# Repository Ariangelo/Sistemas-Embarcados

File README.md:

# Sistemas-Embarcados

Sistemas embarcados são parte integrante de muitos dispositivos de uso cotidiano. por exemplo:
* Sistema eletrônico computacional com propósito específico em controle de dispositivos
* Características importantes
    • Baixo consumo de energia
    • Tamanho reduzido
    • Baixo custopyth

* [Utizando o ESP8266](Documentos/ESP8266.pdf "Dados técnicos básicos para uso do ESP8266")

------

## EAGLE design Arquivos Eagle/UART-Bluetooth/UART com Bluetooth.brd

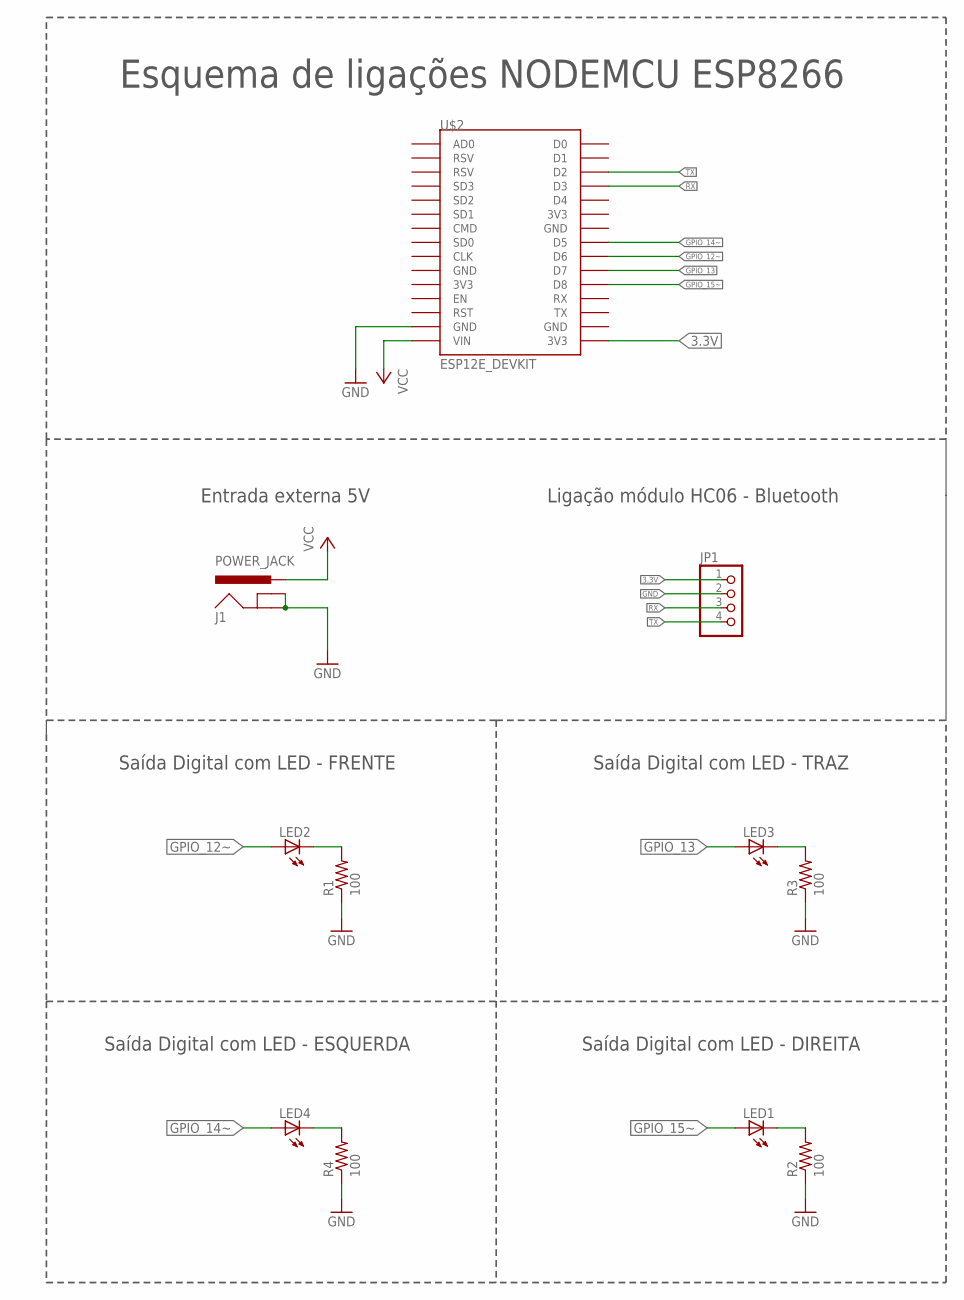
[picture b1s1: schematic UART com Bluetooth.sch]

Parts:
J1: POWER_JACK; POWER_JACK_PTH
JP1: PINHD-1X4; 1X04
LED1, LED2, LED3, LED4: LED5MM
R1, R2, R3, R4: 100; 0204/7
U$2: ESP12E_DEVKIT

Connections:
3.3V: JP1.1, U$2.3V3@2 (3V3)
GND: J1.GND, J1.GNDBREAK, JP1.2, R1.1, R2.1, R3.1, R4.1, U$2.GND@1 (GND)
GPIO_12~: LED2.A, U$2.D6
GPIO_13: LED3.A, U$2.D7
GPIO_14~: LED4.A, U$2.D5
GPIO_15~: LED1.A, U$2.D8
unnamed: LED2.K (C), R1.2
unnamed: LED3.K (C), R3.2
unnamed: LED4.K (C), R4.2
unnamed: LED1.K (C), R2.2
RX: JP1.3, U$2.D3
TX: JP1.4, U$2.D2
VCC: J1.PWR, U$2.VIN

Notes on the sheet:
Saída Digital com LED - DIREITA
Ligação módulo HC06 - Bluetooth
Entrada externa 5V
Esquema de ligações NODEMCU ESP8266
Saída Digital com LED - FRENTE
Saída Digital com LED - TRAZ
Saída Digital com LED - ESQUERDA

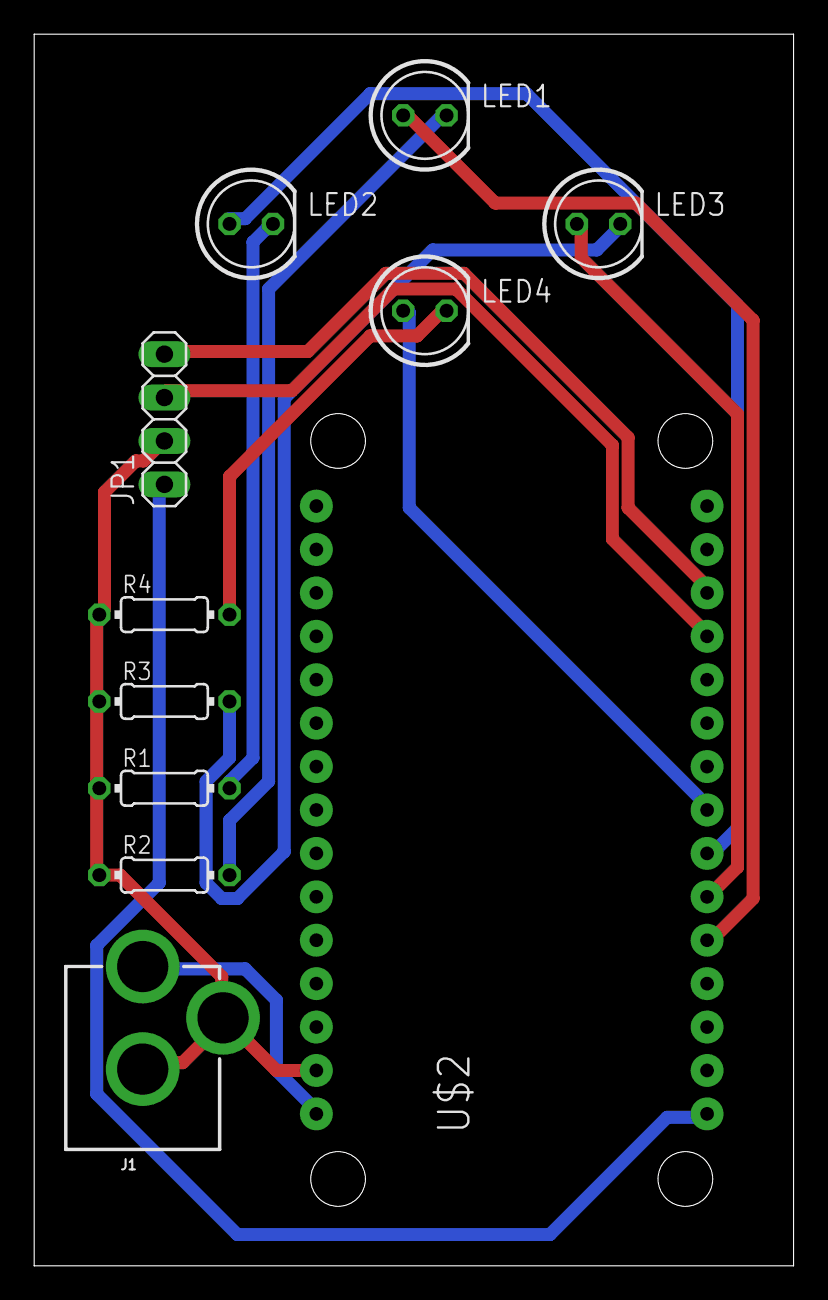
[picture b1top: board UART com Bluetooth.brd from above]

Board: 2 copper layers, 44.4 x 72.1 mm, 11 parts (0 on the bottom side), 13 nets.

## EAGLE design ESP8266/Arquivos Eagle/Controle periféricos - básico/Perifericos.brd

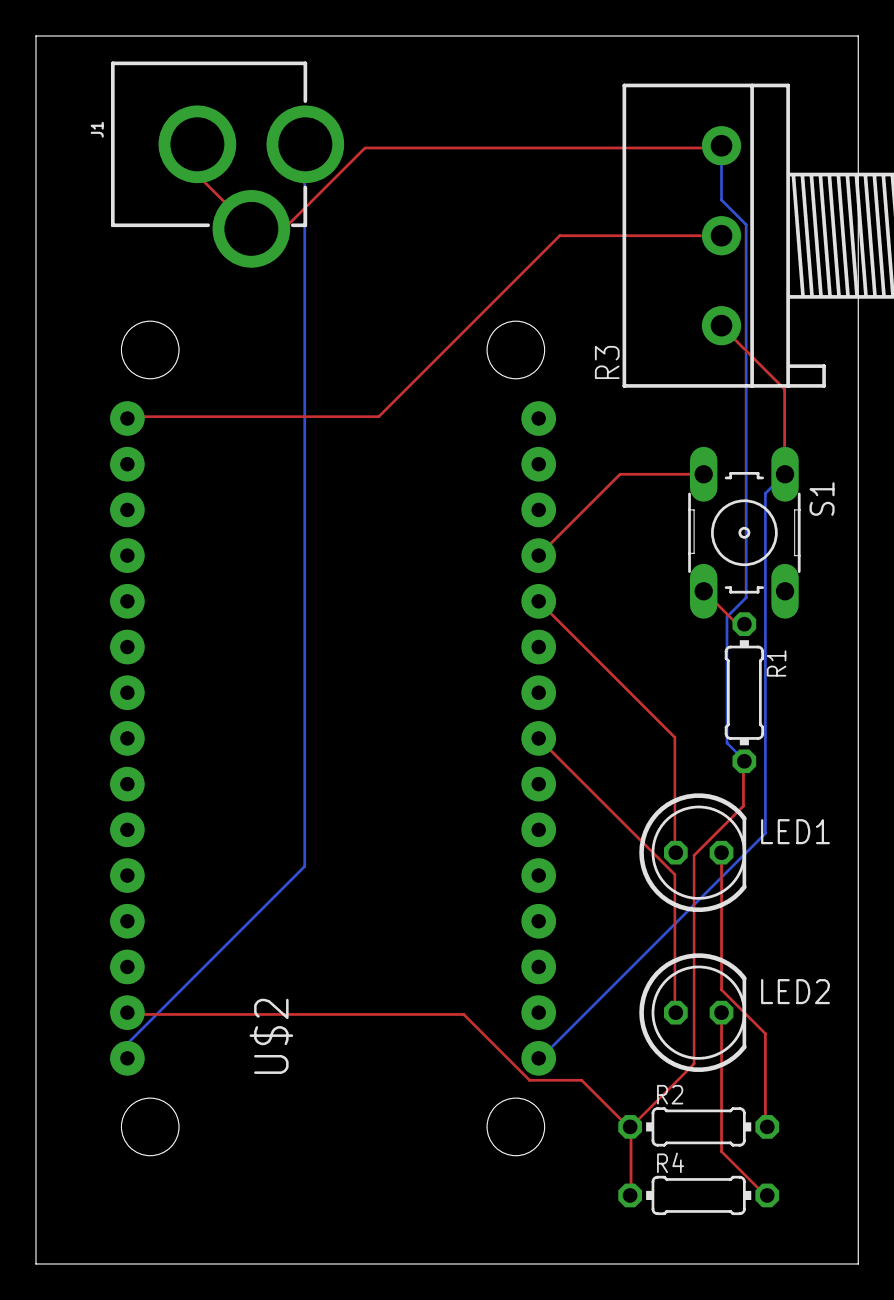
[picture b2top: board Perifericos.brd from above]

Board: 2 copper layers, 45.7 x 68.2 mm, 9 parts (0 on the bottom side), 10 nets.

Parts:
J1: POWER_JACK; POWER_JACK_PTH
LED1, LED2: LED5MM
R1: 100K; 0204/7
R2, R4: 100; 0204/7
R3: 3RP/1610N
S1: B3F-10XX
U$2: ESP12E_DEVKIT

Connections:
3.3V: R3.1, S1.1, U$2.3V3@2
ANALOG: R3.2, U$2.AD0
GND: J1.GND, J1.GNDBREAK, R1.2, R2.1, R3.3, R4.1, U$2.GND@1
GPIO_0: S1.3, U$2.D3
GPIO_2: LED1.A, U$2.D4
GPIO_14~: LED2.A, U$2.D5
unnamed: LED2.K, R4.2
unnamed: R1.1, S1.4
unnamed: LED1.K, R2.2
VCC: J1.PWR, U$2.VIN

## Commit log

2018-08-07 Código fonte para programação ESP8266
    Exemplos
2018-08-07 Arquivos de projeto para realização de testes práticos Eagle
    Exemplos básicos
2018-08-08 Revert "Arquivos de projeto para realização de testes práticos Eagle"
    This reverts commit 817f5a7a4e21f9fa65c1458bd88a18a4e583ed69.
2018-08-16 Atualização - UART
2018-08-16 Atualização esquemas
2018-08-16 Atualização
2018-08-16 Códigos fonte
2018-08-16 Atualizações
2018-08-16 Exclusão
2018-08-21 Comunicação com módulo HC-06 bluetooth
2018-08-21 Ajustes
2018-08-21 Datasheet HC-06 Bluetooth
2018-08-21 Atividade 2 - UART e Bluetooth
2018-08-23 Material apoio aula comunicação WiFi
2018-08-23 Web server ESP8266
2018-08-28 Códigos fonte arduino - ESP8266
2018-08-28 Código fonte ESP8266 Arduino IDE
2018-08-28 Código fonte ESP8266 - IDE Arduino
2018-08-28 Arquivo fonte ESP8266 - UDE Arduino
2018-09-04 Código fonte ESP8266 - Arduino IDE
2018-09-04 Documentos de apoio
2018-09-06 Código fonte ESP8266 - ArduinoIDE
2018-09-06 Biblioteca sensor AM2320 - Arduino IDE
2018-09-11 Documento de apoio MPU-6000 acelerômetro
2018-09-18 Apoio
2018-09-20 Codigo fonte ESP8266 - Arduino IDE
2019-08-01 Alterações
2022-09-30 Atualizção
2022-09-30 Anexar imagem
2022-10-13 Upgrade images
2022-10-13 Upgrade files
2022-10-31 Atualzar
2022-11-28 Andarilho
2022-12-19 atualização python
2022-12-20 atualização simulação

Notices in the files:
parts and their libraries:
SparkFun-Connectors: Licensing: Creative Commons ShareAlike 4.0 International - https://creativecommons.org/licenses/by-sa/4.0
